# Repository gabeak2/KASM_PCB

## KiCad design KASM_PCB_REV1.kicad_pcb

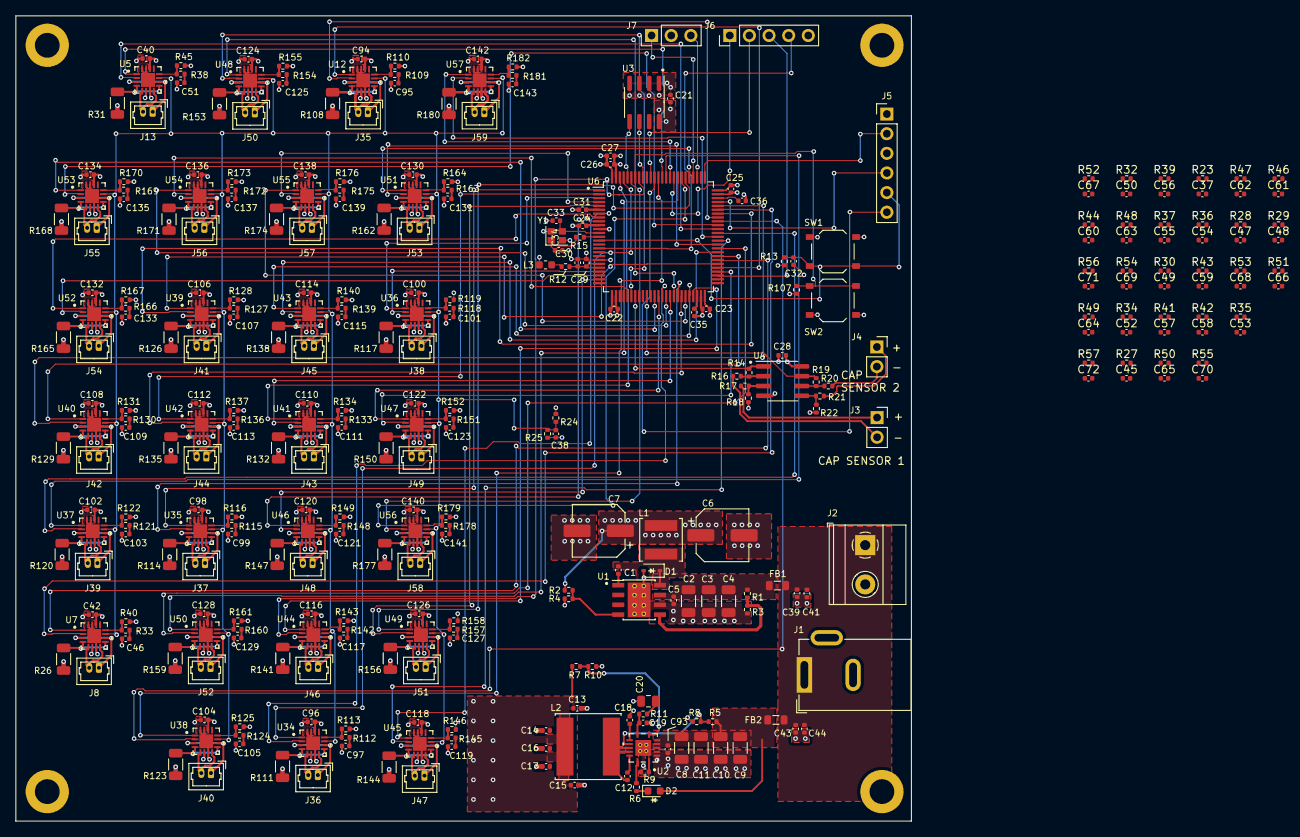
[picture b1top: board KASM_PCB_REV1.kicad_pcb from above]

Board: 4 copper layers, 115.8 x 104.1 mm, 336 parts (0 on the bottom side), 268 nets.

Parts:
C1: 10nF; C_0402_1005Metric
C2, C3, C4, C8, C9, C10, C11: 10uF; C_1206_3216Metric
C5, C12, C21, C22, C23, C24, C25, C26, C28, C29, C31, C32, C37, C39, C40, C42, C44, C45, C47, C48, C49, C50, C52, C53, C54, C55, C56, C57, C58, C59, C60, C61, C62, C63, C64, C65, C66, C67, C68, C69, C70, C71, C72, C93, C94, C96, C98, C100, C102, C104, C106, C108, C110, C112, C114, C116, C118, C120, C122, C124, C126, C128, C130, C132, C134, C136, C138, C140, C142: 100nF; C_0402_1005Metric
C6, C7: 220uF; CP_Elec_6.3x5.4
C13, C14, C15, C16, C17: 22uF; C_0402_1005Metric
C18: 2.2nF; C_0402_1005Metric
C19: 82pF; C_0402_1005Metric
C20: 6.2nF; C_0805_2012Metric
C27, C30, C41, C43: 4.7uF; C_0402_1005Metric
C33, C34: 15pF; C_0402_1005Metric
C35, C36: 2.2uF; C_0402_1005Metric
C38: 1uF; C_0402_1005Metric
C46, C51, C95, C97, C99, C101, C103, C105, C107, C109, C111, C113, C115, C117, C119, C121, C123, C125, C127, C129, C131, C133, C135, C137, C139, C141, C143: 22nF; C_0402_1005Metric
D1: D_Schottky; D_SOD-323
D2: LED; LED_0603_1608Metric
FB1, FB2: FerriteBead_Small; L_0805_2012Metric
H1, H2, H3, H4: MountingHole_Pad; MountingHole_3.2mm_M3_DIN965_Pad
J1: Barrel_Jack_Switch; BarrelJack_GCT_DCJ200-10-A_Horizontal
J2: Screw Terminal; TerminalBlock_Phoenix_MKDS-1,5-2-5.08_1x02_P5.08mm_Horizont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
J3, J4: Conn_01x02; PinSocket_1x02_P2.54mm_Vertical
J5: Conn_01x06; PinHeader_1x06_P2.54mm_Vertical
J6: Conn_01x05; PinHeader_1x05_P2.54mm_Vertical
J7: Conn_01x03; PinHeader_1x03_P2.54mm_Vertical
J8, J13, J35, J36, J37, J38, J39, J40, J41, J42, J43, J44, J45, J46, J47, J48, J49, J50, J51, J52, J53, J54, J55, J56, J57, J58, J59: Picoblade; Molex_PicoBlade_53047-0210_1x02_P1.25mm_Vertical
L1: 56uH; L_Changjiang_FNR5020S
L2: 1.2uH; L_Changjiang_FNR8040S
L3: 100uH; L_0603_1608Metric
R1, R5: 100k; R_0402_1005Metric
R2, R10, R23, R27, R28, R29, R30, R32, R34, R35, R36, R37, R39, R40, R41, R42, R43, R44, R45, R46, R47, R48, R49, R50, R51, R52, R53, R54, R55, R56, R57, R107, R110, R113, R116, R119, R122, R125, R128, R131, R134, R137, R140, R143, R146, R149, R152, R155, R158, R161, R164, R167, R170, R173, R176, R179, R182: 10k; R_0402_1005Metric
R3, R8: 18k; R_0402_1005Metric
R4: 5.9k; R_0402_1005Metric
R6: 4.7k; R_0402_1005Metric
R7: 12.4k; R_0402_1005Metric
R9: 57.6k; R_0402_1005Metric
R11: 3.74k; R_0402_1005Metric
R12: 10; R_0402_1005Metric
R13, R14, R18, R19, R22: 11k; R_0402_1005Metric
R15: 442; R_0402_1005Metric
R16, R17, R20, R21: 33k; R_0402_1005Metric
R24: 5.6k; R_0402_1005Metric
R25, R33, R38, R109, R112, R115, R118, R121, R124, R127, R130, R133, R136, R139, R142, R145, R148, R151, R154, R157, R160, R163, R166, R169, R172, R175, R178, R181: 1k; R_0402_1005Metric
R26, R31, R108, R111, R114, R117, R120, R123, R126, R129, R132, R135, R138, R141, R144, R147, R150, R153, R156, R159, R162, R165, R168, R171, R174, R177, R180: 1.4R; R_1206_3216Metric
SW1, SW2: SW_Push; SW_Push_1P1T_XKB_TS-1187A
U1: TPS5430DDA; TI_SO-PowerPAD-8_ThermalVias
U2: TPS54620; RGY14_2P05X2P05
U3: M24C02-WMN; SOIC-8_3.9x4.9mm_P1.27mm
U4: TLV9062xD; SOIC-8_3.9x4.9mm_P1.27mm
U5, U7, U12, U34, U35, U36, U37, U38, U39, U40, U41, U42, U43, U44, U45, U46, U47, U48, U49, U50, U51, U52, U53, U54, U55, U56, U57: STSPIN250; VFQFPN16_STSPIN_STM
U6: STM32H750VBTx; LQFP-100_14x14mm_P0.5mm
Y1: 24MHz, 9pF; Crystal_SMD_SeikoEpson_FA128-4Pin_2.0x1.6mm

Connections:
+1V8: C13.1, C14.1, C15.1, C16.1, C17.1, C40.1, C42.1, C94.1, C96.1, C98.1, C100.1, C102.1, C104.1, C106.1, C108.1, C110.1, C112.1, C114.1, C116.1, C118.1, C120.1, C122.1, C124.1, C126.1, C128.1, C130.1, C132.1, C134.1, C136.1, C138.1, C140.1, C142.1, L2.2, R7.1, R23.1, R27.1, R28.1, R29.1, R30.1, R32.1, R34.1, R35.1, R36.1, R37.1, R39.1, R41.1, R42.1, R43.1, R44.1, R46.1, R47.1, R48.1, R49.1, R50.1, R51.1, R52.1, R53.1, R54.1, R55.1, R56.1, R57.1, U5.6 (VS), U5.14 (STBY/RESET), U7.6 (VS), U7.14 (STBY/RESET), U12.6 (VS), U12.14 (STBY/RESET), U34.6 (VS), U34.14 (STBY/RESET), U35.6 (VS), U35.14 (STBY/RESET), U36.6 (VS), U36.14 (STBY/RESET), U37.6 (VS), U37.14 (STBY/RESET), U38.6 (VS), U38.14 (STBY/RESET), U39.6 (VS), U39.14 (STBY/RESET), U40.6 (VS), U40.14 (STBY/RESET), U41.6 (VS), U41.14 (STBY/RESET), U42.6 (VS), U42.14 (STBY/RESET), U43.6 (VS), U43.14 (STBY/RESET), U44.6 (VS), U44.14 (STBY/RESET), U45.6 (VS), U45.14 (STBY/RESET), U46.6 (VS), U46.14 (STBY/RESET), U47.6 (VS), U47.14 (STBY/RESET), U48.6 (VS), U48.14 (STBY/RESET), U49.6 (VS), U49.14 (STBY/RESET), U50.6 (VS), U50.14 (STBY/RESET), U51.6 (VS), U51.14 (STBY/RESET), U52.6 (VS), U52.14 (STBY/RESET), U53.6 (VS), U53.14 (STBY/RESET), U54.6 (VS), U54.14 (STBY/RESET), U55.6 (VS), U55.14 (STBY/RESET), U56.6 (VS), U56.14 (STBY/RESET), U57.6 (VS), U57.14 (STBY/RESET)
+3.3V: C6.1, C7.1, C21.1, C22.1, C23.1, C24.1, C25.1, C26.1, C27.2, C28.1, C31.1, J5.1, L1.2, L3.2, R2.1, R13.1, R24.1, SW2.2, U3.8 (VCC), U4.4 (V-), U6.11 (VDD), U6.27 (VDD), U6.50 (VDD), U6.75 (VDD), U6.100 (VDD)
+12V: C39.1, C41.2, C43.2, C44.1, FB1.1, FB2.1, J1.1, J2.1
/Drivers/HRTIM_CHA1/EN: C37.1, R23.2, U57.13 (EN/FLT)
/Drivers/HRTIM_CHA2/EN: C66.1, R51.2, U37.13 (EN/FLT)
/Drivers/HRTIM_CHB1/EN: C72.1, R57.2, U5.13 (EN/FLT)
/Drivers/HRTIM_CHB2/EN: C65.1, R50.2, U38.13 (EN/FLT)
/Drivers/HRTIM_CHC1/EN: C71.1, R56.2, U12.13 (EN/FLT)
/Drivers/HRTIM_CHC2/EN: C64.1, R49.2, U39.13 (EN/FLT)
/Drivers/HRTIM_CHD1/EN: C70.1, R55.2, U7.13 (EN/FLT)
/Drivers/HRTIM_CHD2/EN: C63.1, R48.2, U40.13 (EN/FLT)
/Drivers/LPTIM1_OUT/EN: C53.1, R35.2, U50.13 (EN/FLT)
/Drivers/TIM1_CH1/EN: C69.1, R54.2, U34.13 (EN/FLT)
/Drivers/TIM1_CH2/EN: C62.1, R47.2, U41.13 (EN/FLT)
/Drivers/TIM1_CH3/EN: C68.1, R53.2, U35.13 (EN/FLT)
/Drivers/TIM1_CH4/EN: C61.1, R46.2, U42.13 (EN/FLT)
/Drivers/TIM2_CH1/EN: C67.1, R52.2, U36.13 (EN/FLT)
/Drivers/TIM4_CH1/EN: C60.1, R44.2, U43.13 (EN/FLT)
/Drivers/TIM4_CH2/EN: C59.1, R43.2, U44.13 (EN/FLT)
/Drivers/TIM4_CH3/EN: C52.1, R34.2, U51.13 (EN/FLT)
/Drivers/TIM4_CH4/EN: C58.1, R42.2, U45.13 (EN/FLT)
/Drivers/TIM5_CH2/EN: C50.1, R32.2, U52.13 (EN/FLT)
/Drivers/TIM5_CH3/EN: C57.1, R41.2, U46.13 (EN/FLT)
/Drivers/TIM8_CH4/EN: C49.1, R30.2, U53.13 (EN/FLT)
/Drivers/TIM12_CH2/EN: C56.1, R39.2, U47.13 (EN/FLT)
/Drivers/TIM13_CH1/EN: C48.1, R29.2, U54.13 (EN/FLT)
/Drivers/TIM14_CH1/EN: C55.1, R37.2, U48.13 (EN/FLT)
/Drivers/TIM15_CH1/EN: C47.1, R28.2, U55.13 (EN/FLT)
/Drivers/TIM15_CH2/EN: C54.1, R36.2, U49.13 (EN/FLT)
/Drivers/TIM16_CH1/EN: C45.1, R27.2, U56.13 (EN/FLT)
/MCU/BOOT0: R107.1, SW2.1, U6.94 (BOOT0)
/MCU/CAP_SENSOR_OUT_1: J3.1, R17.2
/MCU/CAP_SENSOR_OUT_2: J4.1, R21.2
/MCU/CAP_SENSOR_RET_1: J3.2, R16.2
/MCU/CAP_SENSOR_RET_2: J4.2, R20.2
/MCU/NRST: C32.1, J5.5, R13.2, SW1.2, U6.14 (NRST)
/MCU/VREF+: C29.1, C30.2, R12.1, U6.20 (VREF+), U6.21 (VDDA)
ADC1_INP4: R14.1, U4.1, U6.32 (PC4)
ADC1_INP5: R19.1, U4.7, U6.35 (PB1)
DEBUG_JTCK-SWCLK: J5.2, U6.76 (PA14)
DEBUG_JTDO-SWO: J5.6, U6.89 (PB3)
DEBUG_JTMS-SWDIO: J5.4, U6.72 (PA13)
GND: C2.2, C3.2, C4.2, C5.2, C6.2, C7.2, C8.2, C9.2, C10.2, C11.2, C13.2, C14.2, C15.2, C16.2, C17.2, C18.2, C19.2, C20.2, C21.2, C22.2, C23.2, C24.2, C25.2, C26.2, C27.1, C28.2, C29.2, C30.1, C32.2, C33.2, C34.2, C35.2, C36.2, C37.2, C38.2, C39.2, C40.2, C41.1, C42.2, C43.1, C44.2, C45.2, C46.2, C47.2, C48.2, C49.2, C50.2, C51.2, C52.2, C53.2, C54.2, C55.2, C56.2, C57.2, C58.2, C59.2, C60.2, C61.2, C62.2, C63.2, C64.2, C65.2, C66.2, C67.2, C68.2, C69.2, C70.2, C71.2, C72.2, C93.2, C94.2, C95.2, C96.2, C97.2, C98.2, C99.2, C100.2, C101.2, C102.2, C103.2, C104.2, C105.2, C106.2, C107.2, C108.2, C109.2, C110.2, C111.2, C112.2, C113.2, C114.2, C115.2, C116.2, C117.2, C118.2, C119.2, C120.2, C121.2, C122.2, C123.2, C124.2, C125.2, C126.2, C127.2, C128.2, C129.2, C130.2, C131.2, C132.2, C133.2, C134.2, C135.2, C136.2, C137.2, C138.2, C139.2, C140.2, C141.2, C142.2, C143.2, D1.2 (A), H1.1, H2.1, H3.1, H4.1, J1.2, J2.2, J5.3, J6.5, J7.2, R3.2, R4.2, R8.2, R9.2, R10.2, R18.2, R22.2, R25.2, R26.2, R31.2, R40.2, R45.2, R107.2, R108.2, R110.2, R111.2, R113.2, R114.2, R116.2, R117.2, R119.2, R120.2, R122.2, R123.2, R125.2, R126.2, R128.2, R129.2, R131.2, R132.2, R134.2, R135.2, R137.2, R138.2, R140.2, R141.2, R143.2, R144.2, R146.2, R147.2, R149.2, R150.2, R152.2, R153.2, R155.2, R156.2, R158.2, R159.2, R161.2, R162.2, R164.2, R165.2, R167.2, R168.2, R170.2, R171.2, R173.2, R174.2, R176.2, R177.2, R179.2, R180.2, R182.2, SW1.1, U1.6 (GND), U1.9 (GNDPAD), U2.2 (GND), U2.3 (GND), U2.15 (PAD_GND), U3.1 (E0), U3.2 (E1), U3.3 (E2), U3.4 (VSS), U4.8 (V+), U5.7 (GND), U5.15 (TEST0), U5.16 (TEST1), U5.17 (EPAD), U6.10 (VSS), U6.19 (VSSA), U6.26 (VSS), U6.49 (VSS), U6.74 (VSS), U6.99 (VSS), U7.7 (GND), U7.15 (TEST0), U7.16 (TEST1), U7.17 (EPAD), U12.7 (GND), U12.15 (TEST0), U12.16 (TEST1), U12.17 (EPAD), U34.7 (GND), U34.15 (TEST0), U34.16 (TEST1), U34.17 (EPAD), U35.7 (GND), U35.15 (TEST0), U35.16 (TEST1), U35.17 (EPAD), U36.7 (GND), U36.15 (TEST0), U36.16 (TEST1), U36.17 (EPAD), U37.7 (GND), U37.15 (TEST0), U37.16 (TEST1), U37.17 (EPAD), U38.7 (GND), U38.15 (TEST0), U38.16 (TEST1), U38.17 (EPAD), U39.7 (GND), U39.15 (TEST0), U39.16 (TEST1), U39.17 (EPAD), U40.7 (GND), U40.15 (TEST0), U40.16 (TEST1), U40.17 (EPAD), U41.7 (GND), U41.15 (TEST0), U41.16 (TEST1), U41.17 (EPAD), U42.7 (GND), U42.15 (TEST0), U42.16 (TEST1), U42.17 (EPAD), U43.7 (GND), U43.15 (TEST0), U43.16 (TEST1), U43.17 (EPAD), U44.7 (GND), U44.15 (TEST0), U44.16 (TEST1), U44.17 (EPAD), U45.7 (GND), U45.15 (TEST0), U45.16 (TEST1), U45.17 (EPAD), U46.7 (GND), U46.15 (TEST0), U46.16 (TEST1), U46.17 (EPAD), U47.7 (GND), U47.15 (TEST0), U47.16 (TEST1), U47.17 (EPAD), U48.7 (GND), U48.15 (TEST0), U48.16 (TEST1), U48.17 (EPAD), U49.7 (GND), U49.15 (TEST0), U49.16 (TEST1), U49.17 (EPAD), U50.7 (GND), U50.15 (TEST0), U50.16 (TEST1), U50.17 (EPAD), U51.7 (GND), U51.15 (TEST0), U51.16 (TEST1), U51.17 (EPAD), U52.7 (GND), U52.15 (TEST0), U52.16 (TEST1), U52.17 (EPAD), U53.7 (GND), U53.15 (TEST0), U53.16 (TEST1), U53.17 (EPAD), U54.7 (GND), U54.15 (TEST0), U54.16 (TEST1), U54.17 (EPAD), U55.7 (GND), U55.15 (TEST0), U55.16 (TEST1), U55.17 (EPAD), U56.7 (GND), U56.15 (TEST0), U56.16 (TEST1), U56.17 (EPAD), U57.7 (GND), U57.15 (TEST0), U57.16 (TEST1), U57.17 (EPAD), Y1.2, Y1.4
HRTIM_CHA1: U6.63 (PC6), U57.2 (PWM)
HRTIM_CHA1_PHASE: U6.85 (PD4), U57.1 (PH)
HRTIM_CHA2: U6.64 (PC7), U37.2 (PWM)
HRTIM_CHA2_PHASE: U6.86 (PD5), U37.1 (PH)
HRTIM_CHB1: U5.2 (PWM), U6.65 (PC8)
HRTIM_CHB1_PHASE: U5.1 (PH), U6.87 (PD6)
HRTIM_CHB2: U6.67 (PA8), U38.2 (PWM)
HRTIM_CHB2_PHASE: U6.88 (PD7), U38.1 (PH)
HRTIM_CHC1: U6.68 (PA9), U12.2 (PWM)
HRTIM_CHC1_PHASE: U6.55 (PD8), U12.1 (PH)
HRTIM_CHC2: U6.69 (PA10), U39.2 (PWM)
HRTIM_CHC2_PHASE: U6.56 (PD9), U39.1 (PH)
HRTIM_CHD1: U6.70 (PA11), U7.2 (PWM)
HRTIM_CHD1_PHASE: U6.57 (PD10), U7.1 (PH)
HRTIM_CHD2: U6.71 (PA12), U40.2 (PWM)
HRTIM_CHD2_PHASE: U6.58 (PD11), U40.1 (PH)
I2C4_SCL: U3.6 (SCL), U6.92 (PB6)
I2C4_SDA: U3.5 (SDA), U6.96 (PB9)
LPTIM1_OUT: U6.60 (PD13), U50.2 (PWM)
LPTIM1_OUT_PHASE: U6.83 (PD2), U50.1 (PH)
unnamed: C12.2, L2.1, U2.11 (PH), U2.12 (PH)
unnamed: C20.1, R11.2
unnamed: C34.1, R15.1, Y1.1
unnamed: C35.1, U6.48 (VCAP)
unnamed: C36.1, U6.73 (VCAP)
unnamed: C46.1, R33.2
unnamed: C51.1, R38.2
unnamed: C95.1, R109.2
unnamed: C97.1, R112.2
unnamed: C99.1, R115.2
unnamed: C101.1, R118.2
unnamed: C103.1, R121.2
unnamed: C105.1, R124.2
unnamed: C107.1, R127.2
unnamed: C109.1, R130.2
unnamed: C111.1, R133.2
unnamed: C113.1, R136.2
unnamed: C115.1, R139.2
unnamed: C117.1, R142.2
unnamed: C119.1, R145.2
unnamed: C121.1, R148.2
unnamed: C123.1, R151.2
unnamed: C125.1, R154.2
unnamed: C127.1, R157.2
unnamed: C129.1, R160.2
unnamed: C131.1, R163.2
unnamed: C133.1, R166.2
unnamed: C135.1, R169.2
unnamed: C137.1, R172.2
unnamed: C139.1, R175.2
unnamed: C141.1, R178.2
unnamed: C143.1, R181.2
unnamed: C1.2, D1.1 (K), L1.1, U1.8 (PH)
unnamed: C8.1, C9.1, C10.1, C11.1, C93.1, D2.2 (A), FB2.2, R5.1, U2.4 (PVIN), U2.5 (PVIN), U2.6 (VIN)
unnamed: D2.1 (K), R6.2
unnamed: J8.1, U7.3 (OUTA1), U7.10 (OUTB1)
unnamed: J8.2, U7.5 (OUTA2), U7.8 (OUTB2)
unnamed: J13.1, U5.3 (OUTA1), U5.10 (OUTB1)
unnamed: J13.2, U5.5 (OUTA2), U5.8 (OUTB2)
unnamed: J35.1, U12.3 (OUTA1), U12.10 (OUTB1)
unnamed: J35.2, U12.5 (OUTA2), U12.8 (OUTB2)
unnamed: J36.1, U34.3 (OUTA1), U34.10 (OUTB1)
unnamed: J36.2, U34.5 (OUTA2), U34.8 (OUTB2)
unnamed: J37.1, U35.3 (OUTA1), U35.10 (OUTB1)
unnamed: J37.2, U35.5 (OUTA2), U35.8 (OUTB2)
unnamed: J38.1, U36.3 (OUTA1), U36.10 (OUTB1)
unnamed: J38.2, U36.5 (OUTA2), U36.8 (OUTB2)
unnamed: J39.1, U37.3 (OUTA1), U37.10 (OUTB1)
unnamed: J39.2, U37.5 (OUTA2), U37.8 (OUTB2)
unnamed: J40.1, U38.3 (OUTA1), U38.10 (OUTB1)
unnamed: J40.2, U38.5 (OUTA2), U38.8 (OUTB2)
unnamed: J41.1, U39.3 (OUTA1), U39.10 (OUTB1)
unnamed: J41.2, U39.5 (OUTA2), U39.8 (OUTB2)
unnamed: J42.1, U40.3 (OUTA1), U40.10 (OUTB1)
unnamed: J42.2, U40.5 (OUTA2), U40.8 (OUTB2)
unnamed: J43.1, U41.3 (OUTA1), U41.10 (OUTB1)
unnamed: J43.2, U41.5 (OUTA2), U41.8 (OUTB2)
unnamed: J44.1, U42.3 (OUTA1), U42.10 (OUTB1)
unnamed: J44.2, U42.5 (OUTA2), U42.8 (OUTB2)
unnamed: J45.1, U43.3 (OUTA1), U43.10 (OUTB1)
unnamed: J45.2, U43.5 (OUTA2), U43.8 (OUTB2)
unnamed: J46.1, U44.3 (OUTA1), U44.10 (OUTB1)
unnamed: J46.2, U44.5 (OUTA2), U44.8 (OUTB2)
unnamed: J47.1, U45.3 (OUTA1), U45.10 (OUTB1)
unnamed: J47.2, U45.5 (OUTA2), U45.8 (OUTB2)
unnamed: J48.1, U46.3 (OUTA1), U46.10 (OUTB1)
unnamed: J48.2, U46.5 (OUTA2), U46.8 (OUTB2)
unnamed: J49.1, U47.3 (OUTA1), U47.10 (OUTB1)
unnamed: J49.2, U47.5 (OUTA2), U47.8 (OUTB2)
unnamed: J50.1, U48.3 (OUTA1), U48.10 (OUTB1)
unnamed: J50.2, U48.5 (OUTA2), U48.8 (OUTB2)
unnamed: J51.1, U49.3 (OUTA1), U49.10 (OUTB1)
unnamed: J51.2, U49.5 (OUTA2), U49.8 (OUTB2)
unnamed: J52.1, U50.3 (OUTA1), U50.10 (OUTB1)
unnamed: J52.2, U50.5 (OUTA2), U50.8 (OUTB2)
unnamed: J53.1, U51.3 (OUTA1), U51.10 (OUTB1)
unnamed: J53.2, U51.5 (OUTA2), U51.8 (OUTB2)
unnamed: J54.1, U52.3 (OUTA1), U52.10 (OUTB1)
unnamed: J54.2, U52.5 (OUTA2), U52.8 (OUTB2)
unnamed: J55.1, U53.3 (OUTA1), U53.10 (OUTB1)
unnamed: J55.2, U53.5 (OUTA2), U53.8 (OUTB2)
unnamed: J56.1, U54.3 (OUTA1), U54.10 (OUTB1)
unnamed: J56.2, U54.5 (OUTA2), U54.8 (OUTB2)
unnamed: J57.1, U55.3 (OUTA1), U55.10 (OUTB1)
unnamed: J57.2, U55.5 (OUTA2), U55.8 (OUTB2)
unnamed: J58.1, U56.3 (OUTA1), U56.10 (OUTB1)
unnamed: J58.2, U56.5 (OUTA2), U56.8 (OUTB2)
unnamed: J59.1, U57.3 (OUTA1), U57.10 (OUTB1)
unnamed: J59.2, U57.5 (OUTA2), U57.8 (OUTB2)
unnamed: L3.1, R12.2
unnamed: C1.1, U1.1 (BOOT)
unnamed: R1.2, R3.1, U1.5 (EN)
unnamed: C2.1, C3.1, C4.1, C5.1, FB1.2, R1.1, U1.7 (VIN)
unnamed: R2.2, R4.1, U1.4 (VSENSE)
unnamed: C12.1, U2.13 (BOOT)
unnamed: C19.1, R11.1, U2.8 (COMP)
unnamed: R5.2, R8.1, U2.10 (EN)
unnamed: R6.1, U2.14 (PWRGD)
unnamed: R9.1, U2.1 (RT/CLK)
unnamed: C18.1, U2.9 (SS/TR)
unnamed: R7.2, R10.1, U2.7 (VSENSE)
unnamed: R17.1, R18.1, U4.3 (+)
unnamed: R14.2, R16.1, U4.2 (-)
unnamed: R21.1, R22.1, U4.5 (+)
unnamed: R19.2, R20.1, U4.6 (-)
unnamed: R31.1, U5.4 (SENSEA), U5.9 (SENSEB)
unnamed: R38.1, R45.1, U5.12 (TOFF)
unnamed: C33.1, U6.12 (PH0), Y1.3
unnamed: R15.2, U6.13 (PH1)
unnamed: C31.2, U6.6 (VBAT)
unnamed: R26.1, U7.4 (SENSEA), U7.9 (SENSEB)
unnamed: R33.1, R40.1, U7.12 (TOFF)
unnamed: R108.1, U12.4 (SENSEA), U12.9 (SENSEB)
unnamed: R109.1, R110.1, U12.12 (TOFF)
unnamed: R111.1, U34.4 (SENSEA), U34.9 (SENSEB)
unnamed: R112.1, R113.1, U34.12 (TOFF)
unnamed: R114.1, U35.4 (SENSEA), U35.9 (SENSEB)
unnamed: R115.1, R116.1, U35.12 (TOFF)
unnamed: R117.1, U36.4 (SENSEA), U36.9 (SENSEB)
unnamed: R118.1, R119.1, U36.12 (TOFF)
unnamed: R120.1, U37.4 (SENSEA), U37.9 (SENSEB)
unnamed: R121.1, R122.1, U37.12 (TOFF)
unnamed: R123.1, U38.4 (SENSEA), U38.9 (SENSEB)
unnamed: R124.1, R125.1, U38.12 (TOFF)
unnamed: R126.1, U39.4 (SENSEA), U39.9 (SENSEB)
unnamed: R127.1, R128.1, U39.12 (TOFF)
unnamed: R129.1, U40.4 (SENSEA), U40.9 (SENSEB)
unnamed: R130.1, R131.1, U40.12 (TOFF)
unnamed: R132.1, U41.4 (SENSEA), U41.9 (SENSEB)
unnamed: R133.1, R134.1, U41.12 (TOFF)
unnamed: R135.1, U42.4 (SENSEA), U42.9 (SENSEB)
unnamed: R136.1, R137.1, U42.12 (TOFF)
unnamed: R138.1, U43.4 (SENSEA), U43.9 (SENSEB)
unnamed: R139.1, R140.1, U43.12 (TOFF)
unnamed: R141.1, U44.4 (SENSEA), U44.9 (SENSEB)
unnamed: R142.1, R143.1, U44.12 (TOFF)
unnamed: R144.1, U45.4 (SENSEA), U45.9 (SENSEB)
unnamed: R145.1, R146.1, U45.12 (TOFF)
unnamed: R147.1, U46.4 (SENSEA), U46.9 (SENSEB)
unnamed: R148.1, R149.1, U46.12 (TOFF)
unnamed: R150.1, U47.4 (SENSEA), U47.9 (SENSEB)
unnamed: R151.1, R152.1, U47.12 (TOFF)
unnamed: R153.1, U48.4 (SENSEA), U48.9 (SENSEB)
unnamed: R154.1, R155.1, U48.12 (TOFF)
unnamed: R156.1, U49.4 (SENSEA), U49.9 (SENSEB)
unnamed: R157.1, R158.1, U49.12 (TOFF)
unnamed: R159.1, U50.4 (SENSEA), U50.9 (SENSEB)
unnamed: R160.1, R161.1, U50.12 (TOFF)
unnamed: R162.1, U51.4 (SENSEA), U51.9 (SENSEB)
unnamed: R163.1, R164.1, U51.12 (TOFF)
unnamed: R165.1, U52.4 (SENSEA), U52.9 (SENSEB)
unnamed: R166.1, R167.1, U52.12 (TOFF)
unnamed: R168.1, U53.4 (SENSEA), U53.9 (SENSEB)
unnamed: R169.1, R170.1, U53.12 (TOFF)
unnamed: R171.1, U54.4 (SENSEA), U54.9 (SENSEB)
unnamed: R172.1, R173.1, U54.12 (TOFF)
unnamed: R174.1, U55.4 (SENSEA), U55.9 (SENSEB)
unnamed: R175.1, R176.1, U55.12 (TOFF)
unnamed: R177.1, U56.4 (SENSEA), U56.9 (SENSEB)
unnamed: R178.1, R179.1, U56.12 (TOFF)
unnamed: R180.1, U57.4 (SENSEA), U57.9 (SENSEB)
unnamed: R181.1, R182.1, U57.12 (TOFF)
REF: C38.1, R24.2, R25.1, U5.11 (REF), U7.11 (REF), U12.11 (REF), U34.11 (REF), U35.11 (REF), U36.11 (REF), U37.11 (REF), U38.11 (REF), U39.11 (REF), U40.11 (REF), U41.11 (REF), U42.11 (REF), U43.11 (REF), U44.11 (REF), U45.11 (REF), U46.11 (REF), U47.11 (REF), U48.11 (REF), U49.11 (REF), U50.11 (REF), U51.11 (REF), U52.11 (REF), U53.11 (REF), U54.11 (REF), U55.11 (REF), U56.11 (REF), U57.11 (REF)
SPI2_MISO: J6.3, U6.53 (PB14)
SPI2_MOSI: J6.4, U6.16 (PC1)
SPI2_NSS: J6.2, U6.90 (PB4)
SPI2_SCK: J6.1, U6.84 (PD3)
TIM1_CH1: U6.39 (PE9), U34.2 (PWM)
TIM1_CH1_PHASE: U6.97 (PE0), U34.1 (PH)
TIM1_CH2: U6.41 (PE11), U41.2 (PWM)
TIM1_CH2_PHASE: U6.98 (PE1), U41.1 (PH)
TIM1_CH3: U6.43 (PE13), U35.2 (PWM)
TIM1_CH3_PHASE: U6.1 (PE2), U35.1 (PH)
TIM1_CH4: U6.44 (PE14), U42.2 (PWM)
TIM1_CH4_PHASE: U6.2 (PE3), U42.1 (PH)
TIM2_CH1: U6.22 (PA0), U36.2 (PWM)
TIM2_CH1_PHASE: U6.3 (PE4), U36.1 (PH)
TIM4_CH1: U6.59 (PD12), U43.2 (PWM)
TIM4_CH1_PHASE: U6.46 (PB10), U43.1 (PH)
TIM4_CH2: U6.93 (PB7), U44.2 (PWM)
TIM4_CH2_PHASE: U6.47 (PB11), U44.1 (PH)
TIM4_CH3: U6.61 (PD14), U51.2 (PWM)
TIM4_CH3_PHASE: U6.80 (PC12), U51.1 (PH)
TIM4_CH4: U6.62 (PD15), U45.2 (PWM)
TIM4_CH4_PHASE: U6.7 (PC13), U45.1 (PH)
TIM5_CH2: U6.23 (PA1), U52.2 (PWM)
TIM5_CH2_PHASE: U6.8 (PC14), U52.1 (PH)
TIM5_CH3: U6.24 (PA2), U46.2 (PWM)
TIM5_CH3_PHASE: U6.9 (PC15), U46.1 (PH)
TIM8_CH4: U6.66 (PC9), U53.2 (PWM)
TIM8_CH4_PHASE: U6.37 (PE7), U53.1 (PH)
TIM12_CH2: U6.54 (PB15), U47.2 (PWM)
TIM12_CH2_PHASE: U6.38 (PE8), U47.1 (PH)
TIM13_CH1: U6.30 (PA6), U54.2 (PWM)
TIM13_CH1_PHASE: U6.40 (PE10), U54.1 (PH)
TIM14_CH1: U6.31 (PA7), U48.2 (PWM)
TIM14_CH1_PHASE: U6.42 (PE12), U48.1 (PH)
TIM15_CH1: U6.4 (PE5), U55.2 (PWM)
TIM15_CH1_PHASE: U6.45 (PE15), U55.1 (PH)
TIM15_CH2: U6.5 (PE6), U49.2 (PWM)
TIM15_CH2_PHASE: U6.81 (PD0), U49.1 (PH)
TIM16_CH1: U6.95 (PB8), U56.2 (PWM)
TIM16_CH1_PHASE: U6.82 (PD1), U56.1 (PH)
UART4_RX: J7.1, U6.79 (PC11)
UART4_TX: J7.3, U6.78 (PC10)

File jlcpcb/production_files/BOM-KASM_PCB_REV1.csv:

Comment,Designator,Footprint,LCSC
FerriteBead_Small,"FB1,FB2",L_0805_2012Metric,C1017
82pF,C19,C_0402_1005Metric,C107011
12.4k,R7,R_0402_1005Metric,C11692
1k,"R109,R112,R115,R118,R121,R124,R127,R130,R133,R136,R139,R142,R145,R148,R151,R154,R157,R160,R163,R166,R169,R172,R175,R178,R181,R25,R33,R38",R_0402_1005Metric,C11702
2.2uF,"C35,C36",C_0402_1005Metric,C12530
442,R15,R_0402_1005Metric,C126137
18k,"R3,R8",R_0402_1005Metric,C138044
3.74k,R11,R_0402_1005Metric,C15172
10nF,"C37,C45,C47,C48,C49,C50,C52,C53,C54,C55,C56,C57,C58,C59,C60,C61,C62,C63,C64,C65,C66,C67,C68,C69,C70,C71,C72",C_0402_1005Metric,C15195
100nF,"C100,C102,C104,C106,C108,C110,C112,C114,C116,C118,C12,C120,C122,C124,C126,C128,C130,C132,C134,C136,C138,C140,C142,C21,C22,C23,C24,C25,C26,C28,C29,C31,C32,C39,C40,C42,C44,C5,C93,C94,C96,C98",C_0402_1005Metric,C1525
2.2nF,"C18,C73,C74,C75,C76",C_0402_1005Metric,C1531
22nF,"C101,C103,C105,C107,C109,C111,C113,C115,C117,C119,C121,C123,C125,C127,C129,C131,C133,C135,C137,C139,C141,C143,C46,C51,C95,C97,C99",C_0402_1005Metric,C1532
15pF,"C33,C34",C_0402_1005Metric,C1548
STSPIN250,"U12,U34,U35,U36,U37,U38,U39,U40,U41,U42,U43,U44,U45,U46,U47,U48,U49,U5,U50,U51,U52,U53,U54,U55,U56,U57,U7",VFQFPN16_STSPIN_STM,C155561
Barrel_Jack_Switch,J1,BarrelJack_GCT_DCJ200-10-A_Horizontal,C16214
56uH,L1,L_Changjiang_FNR5020S,C167944
1.2uH,L2,L_Changjiang_FNR8040S,C168113
1.0R,"R108,R111,R114,R117,R120,R123,R126,R129,R132,R135,R138,R141,R144,R147,R150,R153,R156,R159,R162,R165,R168,R171,R174,R177,R180,R26,R31",R_1206_3216Metric,C17928
D_Schottky,D1,D_SOD-323,C191023
LED,D2,LED_0603_1608Metric,C2286
4.7uF,"C27,C30",C_0402_1005Metric,C23733
100k,"R1,R5",R_0402_1005Metric,C25741
10k,"R10,R107,R110,R113,R116,R119,R122,R125,R128,R131,R134,R137,R140,R143,R146,R149,R152,R155,R158,R161,R164,R167,R170,R173,R176,R179,R182,R2,R23,R27,R28,R29,R30,R32,R34,R35,R36,R37,R39,R40,R41,R42,R43,R44,R45,R46,R47,R48,R49,R50,R51,R52,R53,R54,R55,R56,R57",R_0402_1005Metric,C25744
11k,"R13,R14,R18,R19,R22",R_0402_1005Metric,C25749
33k,"R16,R17,R20,R21",R_0402_1005Metric,C25779
4.7k,R6,R_0402_1005Metric,C25900
5.6k,R24,R_0402_1005Metric,C25908
57.6k,R9,R_0402_1005Metric,C26983
5.9k,R4,R_0402_1005Metric,C270591
"24MHz, 9pF",Y1,Crystal_SMD_SeikoEpson_FA128-4Pin_2.0x1.6mm,C2929399
TPS54620,U2,RGY14_2P05X2P05,C29438
6.2nF,C20,C_0805_2012Metric,C3037648
SW_Push,"SW1,SW2",SW_Push_1P1T_XKB_TS-1187A,C318884
TLV9062xD,U4,SOIC-8_3.9x4.9mm_P1.27mm,C398355
STM32H750VBTx,U6,LQFP-100_14x14mm_P0.5mm,C404010
10,R12,R_0402_1005Metric,C409845
22uF,"C13,C14,C15,C16,C17",C_0402_1005Metric,C415703
10uF,"C10,C11,C2,C3,C4,C41,C43,C8,C9",C_1206_3216Metric,C454102
100uH,L3,L_0603_1608Metric,C51942
1uF,C38,C_0402_1005Metric,C52923
Screw Terminal,J2,"TerminalBlock_Phoenix_MKDS-1,5-2-5.08_1x02_P5.08mm_Horizontal",C557646
220uF,"C6,C7",CP_Elec_6.3x5.4,C59953
10nF,C1,C_0402_1005Metric,C60133
M24C02-WMN,U3,SOIC-8_3.9x4.9mm_P1.27mm,C7562
TPS5430DDA,U1,TI_SO-PowerPAD-8_ThermalVias,C9864
Picoblade,J38,Molex_PicoBlade_53047-0210_1x02_P1.25mm_Vertical,
Conn_01x03,J7,PinHeader_1x03_P2.54mm_Vertical,
Picoblade,J44,Molex_PicoBlade_53047-0210_1x02_P1.25mm_Vertical,
MountingHole_Pad,H2,MountingHole_3.2mm_M3_DIN965_Pad,
Picoblade,J8,Molex_PicoBlade_53047-0210_1x02_P1.25mm_Vertical,
Picoblade,J40,Molex_PicoBlade_53047-0210_1x02_P1.25mm_Vertical,
Conn_01x06,J5,PinHeader_1x06_P2.54mm_Vertical,
Picoblade,J35,Molex_PicoBlade_53047-0210_1x02_P1.25mm_Vertical,
MountingHole_Pad,H4,MountingHole_3.2mm_M3_DIN965_Pad,
Picoblade,J13,Molex_PicoBlade_53047-0210_1x02_P1.25mm_Vertical,
Picoblade,J48,Molex_PicoBlade_53047-0210_1x02_P1.25mm_Vertical,
Picoblade,J43,Molex_PicoBlade_53047-0210_1x02_P1.25mm_Vertical,
Picoblade,J52,Molex_PicoBlade_53047-0210_1x02_P1.25mm_Vertical,
Picoblade,J50,Molex_PicoBlade_53047-0210_1x02_P1.25mm_Vertical,
Picoblade,J56,Molex_PicoBlade_53047-0210_1x02_P1.25mm_Vertical,
Conn_01x02,J3,PinSocket_1x02_P2.54mm_Vertical,
Picoblade,J37,Molex_PicoBlade_53047-0210_1x02_P1.25mm_Vertical,
Picoblade,J54,Molex_PicoBlade_53047-0210_1x02_P1.25mm_Vertical,
Picoblade,J41,Molex_PicoBlade_53047-0210_1x02_P1.25mm_Vertical,
Picoblade,J58,Molex_PicoBlade_53047-0210_1x02_P1.25mm_Vertical,
Picoblade,J46,Molex_PicoBlade_53047-0210_1x02_P1.25mm_Vertical,
Conn_01x05,J6,PinHeader_1x05_P2.54mm_Vertical,
Picoblade,J53,Molex_PicoBlade_53047-0210_1x02_P1.25mm_Vertical,
Picoblade,J45,Molex_PicoBlade_53047-0210_1x02_P1.25mm_Vertical,
Picoblade,J42,Molex_PicoBlade_53047-0210_1x02_P1.25mm_Vertical,
Picoblade,J51,Molex_PicoBlade_53047-0210_1x02_P1.25mm_Vertical,
Picoblade,J39,Molex_PicoBlade_53047-0210_1x02_P1.25mm_Vertical,
MountingHole_Pad,H1,MountingHole_3.2mm_M3_DIN965_Pad,
Conn_01x02,J4,PinSocket_1x02_P2.54mm_Vertical,
Picoblade,J57,Molex_PicoBlade_53047-0210_1x02_P1.25mm_Vertical,
Picoblade,J36,Molex_PicoBlade_53047-0210_1x02_P1.25mm_Vertical,
Picoblade,J59,Molex_PicoBlade_53047-0210_1x02_P1.25mm_Vertical,
MountingHole_Pad,H3,MountingHole_3.2mm_M3_DIN965_Pad,
Picoblade,J55,Molex_PicoBlade_53047-0210_1x02_P1.25mm_Vertical,
Picoblade,J49,Molex_PicoBlade_53047-0210_1x02_P1.25mm_Vertical,
Picoblade,J47,Molex_PicoBlade_53047-0210_1x02_P1.25mm_Vertical,
